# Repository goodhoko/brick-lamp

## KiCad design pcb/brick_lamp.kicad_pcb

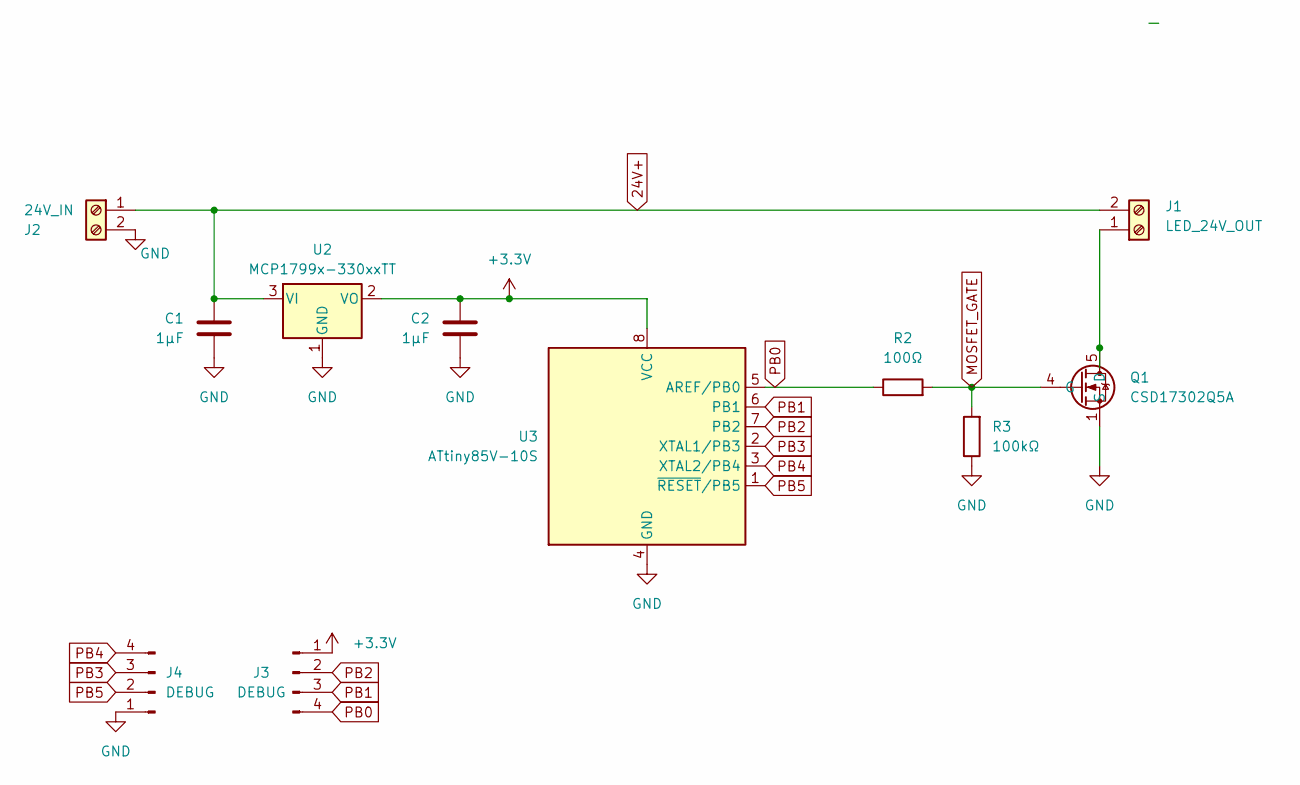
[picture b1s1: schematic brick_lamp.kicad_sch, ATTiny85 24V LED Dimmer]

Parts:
C1, C2: 1μF; C_0805_2012Metric; LCSC C28323
J1: LED_24V_OUT; TerminalBlock_Phoenix_MPT-0,5-2-2.54_1x02_P2.54mm_Horizontal
J2: 24V_IN; TerminalBlock_Phoenix_MPT-0,5-2-2.54_1x02_P2.54mm_Horizontal
J3, J4: DEBUG; PinHeader_1x04_P2.54mm_Vertical
Q1: CSD17302Q5A; TDSON-8-1; LCSC C553151
R2: 100Ω; C_0805_2012Metric; LCSC C17408
R3: 100kΩ; C_0805_2012Metric; LCSC C149504
U2: MCP1799x-330xxTT; SOT-23; LCSC C486069
U3: ATtiny85V-10S; SOIC-8_5.3x5.3mm_P1.27mm; LCSC C152192

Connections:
24V+: C1.1, J1.2, J2.1, U2.3 (VI)
+3.3V: C2.1, J3.1, U2.2 (VO), U3.8 (VCC)
GND: C1.2, C2.2, J2.2, J4.1, Q1.1 (S), Q1.2 (S), Q1.3 (S), R3.1, U2.1 (GND), U3.4 (GND)
MOSFET_GATE: Q1.4 (G), R2.2, R3.2
unnamed: J1.1, Q1.5 (D)
PB0: J3.4, R2.1, U3.5 (AREF/PB0)
PB1: J3.3, U3.6 (PB1)
PB2: J3.2, U3.7 (PB2)
PB3: J4.3, U3.2 (XTAL1/PB3)
PB4: J4.4, U3.3 (XTAL2/PB4)
PB5: J4.2, U3.1 (~RESET/PB5)

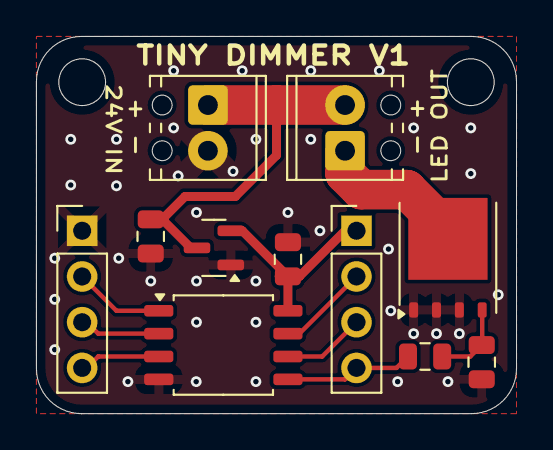
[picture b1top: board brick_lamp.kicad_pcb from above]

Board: 2 copper layers, 26.7 x 21.0 mm, 11 parts (0 on the bottom side), 11 nets.

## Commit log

2025-10-05 Kickoff I guess
2025-10-05 More references
2025-10-17 Add PCB design
2025-10-17 Cleanup the layout and schematic
2025-10-17 Fill in schematic sheet details
2025-10-17 Ignore another temporary kicad file
2025-10-17 Some more PCB cleanup
2025-10-22 Cleanup schematics
2025-10-23 Add CSpell dictionary
2025-10-23 Use potentiometer as input, average over multiple samples
2025-10-23 Add name of the board to silkscreen; improve current capacity
2025-10-24 Gamma correct
2025-10-24 Make the two pin headers breadboard compatible
2025-10-25 Make it tiny not tinny
2025-10-25 Final cleanups for production
2025-10-29 Remove forgotten unconnected lines
2025-11-03 Split Potentiometer into its own module
2025-11-30 Work around simple PWM not reachin pure zero output
2025-12-01 Document a flashing error
2025-12-01 Simplify potentiometer code
    testing showed that the averaging doesn't really do anything
2025-12-01 Simplify the "PWM enable" block
    no functional change, just indentation and comment tweaks
2025-12-01 Improve legibility of unsafe code
2025-12-01 Init input first, then output
2025-12-01 Factor PWM inverting to a separate module
2025-12-07 Add the most basic hysteresis to tackle flicker
2025-12-10 Add simple temporal dithering and cap power at 80%
2025-12-10 Smooth over ADC boundary flicker
2025-12-10 Mention a TODO of using higher gamma
